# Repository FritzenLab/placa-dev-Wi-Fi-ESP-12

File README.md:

Placa de prototipagem Wi-Fi com ESP-12 (ESP8266)

TODA INFORMAÇÃO sobre esta placa de desenvolvimento Wi-FI ESP-12 está concentrada neste post do FritzenLab:
https://fritzenlab.com.br/2018/07/placa-de-desenvolvimento-wifi-esp12/ e aqui: 
https://fritzenlab.com.br/2016/03/wifi-esp12-esp8266-programando-com-a-ide-do-arduino/

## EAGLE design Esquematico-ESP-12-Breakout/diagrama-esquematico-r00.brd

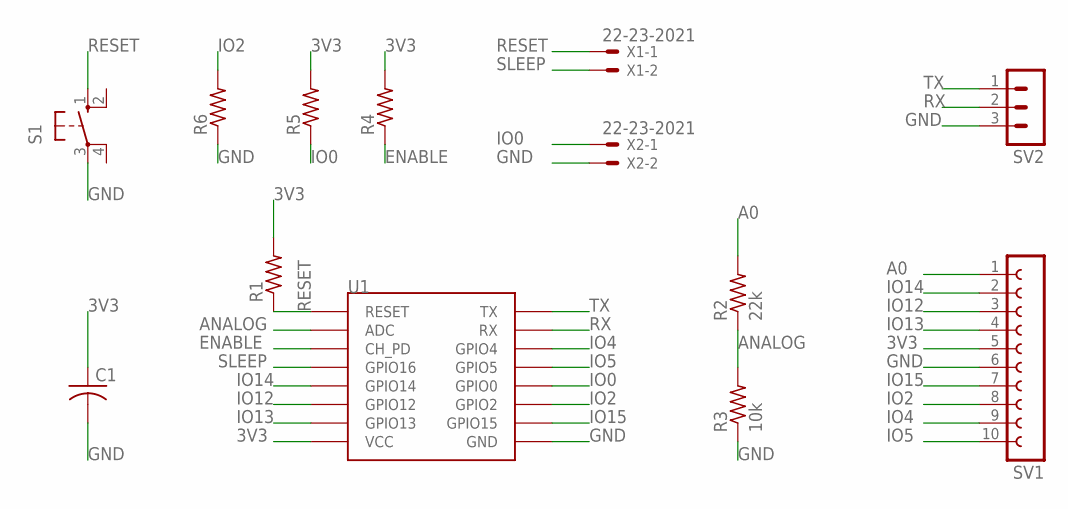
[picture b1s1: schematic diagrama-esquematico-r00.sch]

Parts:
C1: C-US025-030X050; C025-030X050
R1, R4, R5, R6: R-US_0207/10; 0207/10
R2: 22k; 0207/10
R3: 10k; 0207/10
S1: 10-XX; B3F-10XX
SV1: FE10-1; FE10
SV2: MA03-1
U1: ESP12
X1, X2: 22-23-2021

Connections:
3V3: C1.1, R1.2, R4.2, R5.2, SV1.5, U1.VCC
A0: R2.2, SV1.1
ANALOG: R2.1, R3.2, U1.ADC
ENABLE: R4.1, U1.CH_PD
GND: C1.2, R3.1, R6.1, S1.3, SV1.6, SV2.3, U1.GND, X2.2
IO0: R5.1, U1.GPIO0, X2.1
IO2: R6.2, SV1.8, U1.GPIO2
IO4: SV1.9, U1.GPIO4
IO5: SV1.10, U1.GPIO5
IO12: SV1.3, U1.GPIO12
IO13: SV1.4, U1.GPIO13
IO14: SV1.2, U1.GPIO14
IO15: SV1.7, U1.GPIO15
RESET: R1.1, S1.1 (S), U1.RESET, X1.1
RX: SV2.2, U1.RX
SLEEP: U1.GPIO16, X1.2
TX: SV2.1, U1.TX

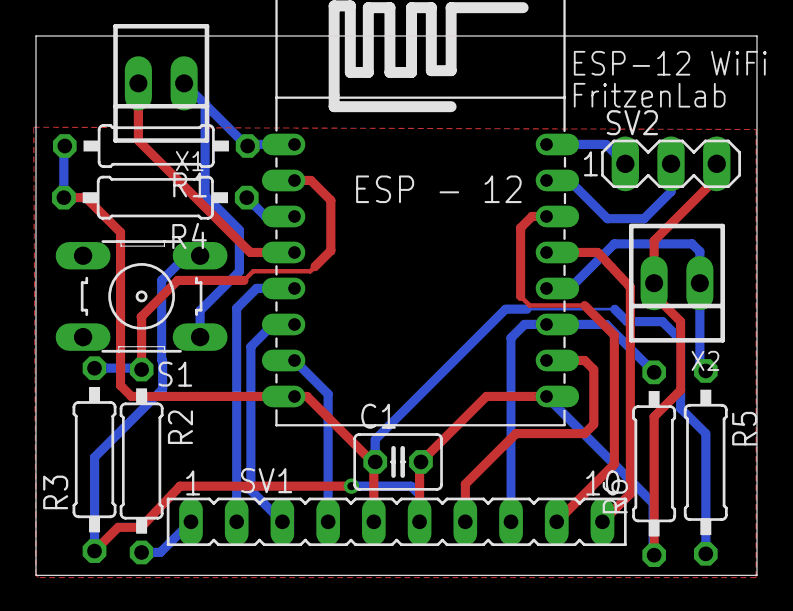
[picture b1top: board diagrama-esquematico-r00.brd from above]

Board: 2 copper layers, 40.1 x 30.0 mm, 13 parts (0 on the bottom side), 17 nets.

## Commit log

2018-07-28 primeiro commit
2018-07-28 adicionado esquematico
2018-07-28 criado read-me
    criado read-me
2018-07-29 alterado read-me
    alterado read-me
2019-03-05 revisão r01
    revisão r01, adicionados pinos ao conector de interface
